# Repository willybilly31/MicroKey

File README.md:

# MicroKey
ATmega32U4-AU based micro controller with the sole purpose of emulating keyboard and mouse input. This project was made for Hack Club forge. The idea came to me when i was playing with my Esp32-S3 and thought the keyboard emulation with HID was cool, but the form factor of the Esp32 was too big and i also wanted to make my own devboard and thought this would be simple.

## Hardware
- ATmega32U4-AU
- Power Led
- User input Led
- USB C receptacle
- 16mhz Crystal
- Generic 2x3 header for bootloader

## Features
- HID emulation with the ATmega32U4-AU
- User input light

## Screenshots

## BOM 
﻿<table>
  <thead>
    <tr>
      <th>Designator</th>
      <th>Footprint</th>
      <th>Quantity</th>
      <th>Value</th>
      <th>LCSC Part #</th>
      <th>Minimum Price</th>
      <th>LCSC Link</th>
    </tr>
  </thead>
  <tbody>
    <tr>
      <td>C1, C2</td>
      <td>0603</td>
      <td>2</td>
      <td>27pF</td>
      <td>C1656</td>
      <td>0.60$</td>
      <td><a href="https://www.lcsc.com/product-detail/C1656.html">C1656</a></td>
    </tr>
    <tr>
      <td>C10, C3, C4, C5, C6, C9</td>
      <td>0603</td>
      <td>6</td>
      <td>100nF</td>
      <td>C1591</td>
      <td>0.28$</td>
      <td><a href="https://www.lcsc.com/product-detail/C1591.html">C1591</a></td>
    </tr>
    <tr>
      <td>C7</td>
      <td>0603</td>
      <td>1</td>
      <td>10uF</td>
      <td>C19702</td>
      <td>0.40$</td>
      <td><a href="https://www.lcsc.com/product-detail/C19702.html">C19702</a></td>
    </tr>
    <tr>
      <td>C8</td>
      <td>0603</td>
      <td>1</td>
      <td>1uF</td>
      <td>C15849</td>
      <td>0.87$</td>
      <td><a href="https://www.lcsc.com/product-detail/C15849.html">C15849</a></td>
    </tr>
    <tr>
      <td>D1</td>
      <td>0603</td>
      <td>1</td>
      <td>RED</td>
      <td>C2286</td>
      <td>0.0076$</td>
      <td><a href="https://www.lcsc.com/product-detail/C2286.html">C2286</a></td>
    </tr>
    <tr>
      <td>D2</td>
      <td>0603</td>
      <td>1</td>
      <td>BLUE</td>
      <td>C965807</td>
      <td>0.0043$</td>
      <td><a href="https://www.lcsc.com/product-detail/C965807.html">C965807</a></td>
    </tr>
    <tr>
      <td>J1</td>
      <td>GCT_USB4105-GF-A</td>
      <td>1</td>
      <td>USB_C_Receptacle_USB2.0_16P</td>
      <td>C5184243</td>
      <td></td>
      <td><a href="https://www.lcsc.com/product-detail/C5184243.html">C5184243</a></td>
    </tr>
    <tr>
      <td>J2</td>
      <td>AVR_ISP_2x3_Pogo_3p23x1p80</td>
      <td>1</td>
      <td>Conn_02x03_Odd_Even</td>
      <td></td>
      <td></td>
      <td></td>
    </tr>
    <tr>
      <td>R1, R2</td>
      <td>0603</td>
      <td>2</td>
      <td>5.1k</td>
      <td>C23186</td>
      <td>0.12$</td>
      <td><a href="https://www.lcsc.com/product-detail/C23186.html">C23186</a></td>
    </tr>
    <tr>
      <td>R3, R4</td>
      <td>0603</td>
      <td>2</td>
      <td>22</td>
      <td>C23345</td>
      <td>0.0018$</td>
      <td><a href="https://www.lcsc.com/product-detail/C23345.html">C23345</a></td>
    </tr>
    <tr>
      <td>R5, R6</td>
      <td>0603</td>
      <td>2</td>
      <td>1k</td>
      <td>C21190</td>
      <td>0.06$</td>
      <td><a href="https://www.lcsc.com/product-detail/C21190.html">C21190</a></td>
    </tr>
    <tr>
      <td>R7, R8</td>
      <td>0603</td>
      <td>2</td>
      <td>10k</td>
      <td>C25804</td>
      <td>0.09$</td>
      <td><a href="https://www.lcsc.com/product-detail/C25804.html">C25804</a></td>
    </tr>
    <tr>
      <td>U1</td>
      <td>TQFP-44_10x10mm_P0.8mm</td>
      <td>1</td>
      <td>ATmega32U4-A</td>
      <td>C44854</td>
      <td>6.94$</td>
      <td><a href="https://www.lcsc.com/product-detail/C44854.html">C44854</a></td>
    </tr>
    <tr>
      <td>Y1</td>
      <td>Crystal_SMD_3225-4Pin_3.2x2.5mm</td>
      <td>1</td>
      <td>16MHz</td>
      <td>C70562</td>
      <td>0.55$</td>
      <td><a href="https://www.lcsc.com/product-detail/C70562.html">C70562</a></td>
    </tr>
  </tbody>
</table>

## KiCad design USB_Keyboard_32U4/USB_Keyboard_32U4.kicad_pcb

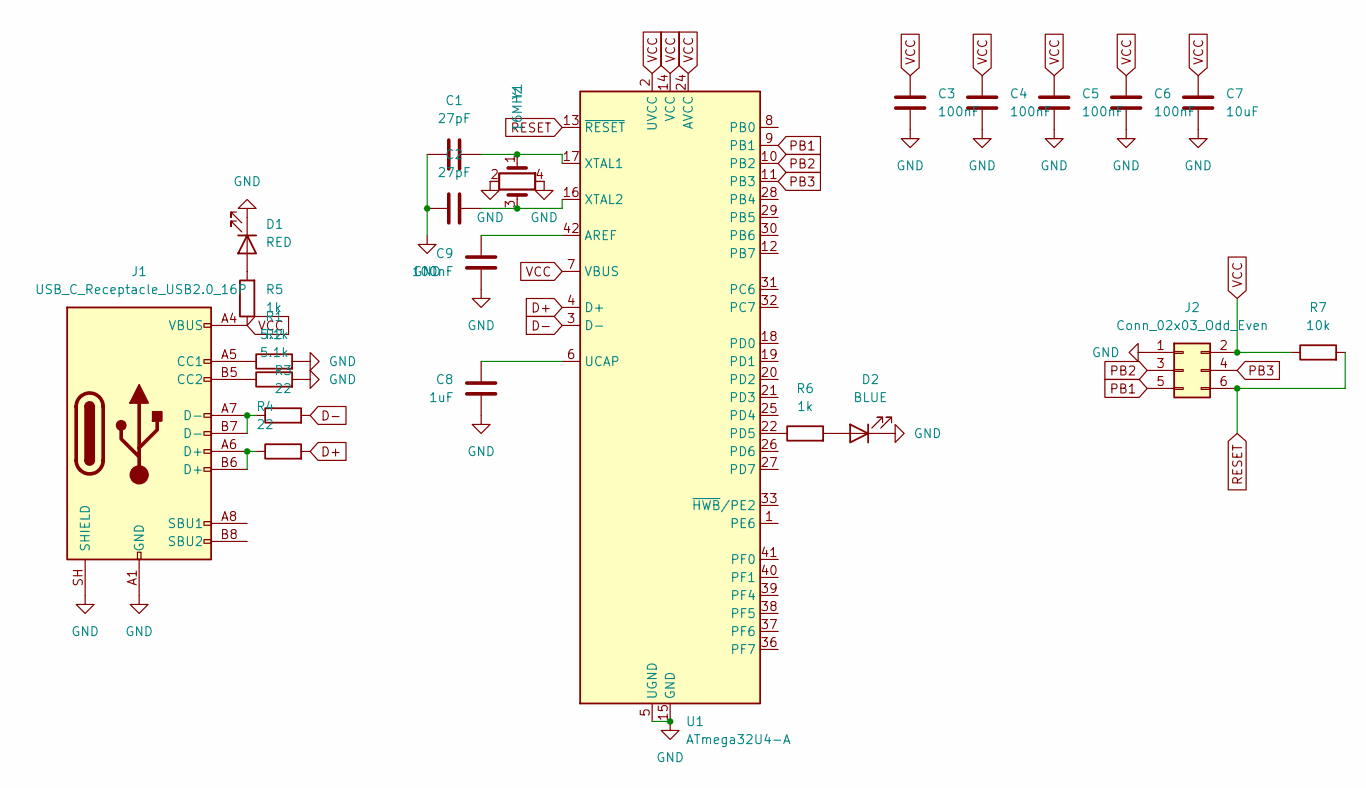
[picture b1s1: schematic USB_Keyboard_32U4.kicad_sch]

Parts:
C1, C2: 27pF; C_0603_1608Metric_Pad1.08x0.95mm_HandSolder
C3, C4, C5, C6, C9: 100nF; C_0603_1608Metric_Pad1.08x0.95mm_HandSolder
C7: 10uF; C_0603_1608Metric_Pad1.08x0.95mm_HandSolder
C8: 1uF; C_0603_1608Metric_Pad1.08x0.95mm_HandSolder
D1: RED; LED_0603_1608Metric_Pad1.05x0.95mm_HandSolder
D2: BLUE; LED_0603_1608Metric_Pad1.05x0.95mm_HandSolder
J1: USB_C_Receptacle_USB2.0_16P; GCT_USB4105-GF-A
J2: Conn_02x03_Odd_Even; AVR_ISP_2x3_Pogo_3p23x1p80
R1, R2: 5.1k; R_0603_1608Metric_Pad0.98x0.95mm_HandSolder
R3, R4: 22; R_0603_1608Metric_Pad0.98x0.95mm_HandSolder
R5, R6: 1k; R_0603_1608Metric_Pad0.98x0.95mm_HandSolder
R7: 10k; R_0603_1608Metric_Pad0.98x0.95mm_HandSolder
U1: ATmega32U4-A; TQFP-44_10x10mm_P0.8mm
Y1: 16MHz; Crystal_SMD_3225-4Pin_3.2x2.5mm

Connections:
D+: R4.2, U1.4 (D+)
D-: R3.2, U1.3 (D-)
GND: C1.1, C2.1, C3.2, C4.2, C5.2, C6.2, C7.2, C8.2, C9.2, D1.1 (K), D2.1 (K), J1.A1 (GND), J1.A12 (GND), J1.B1 (GND), J1.B12 (GND), J1.SH (SHIELD), J2.1, R1.2, R2.2, U1.5 (UGND), U1.15 (GND), U1.23 (GND), U1.35 (GND), U1.43 (GND), Y1.2, Y1.4; also elsewhere on the board
unnamed: D1.2 (A), R5.2
unnamed: D2.2 (A), R6.2
unnamed: J1.A5 (CC1), R1.1
unnamed: J1.B5 (CC2), R2.1
unnamed: J1.A6 (D+), J1.B6 (D+), R4.1
unnamed: J1.A7 (D-), J1.B7 (D-), R3.1
unnamed: C9.1, U1.42 (AREF)
unnamed: R6.1, U1.22 (PD5)
unnamed: C8.1, U1.6 (UCAP)
unnamed: C1.2, U1.17 (XTAL1), Y1.1
unnamed: C2.2, U1.16 (XTAL2), Y1.3
PB1: J2.5, U1.9 (PB1)
PB2: J2.3, U1.10 (PB2)
PB3: J2.4, U1.11 (PB3)
RESET: J2.6, R7.2, U1.13 (~RESET)
VCC: C3.1, C4.1, C5.1, C6.1, C7.1, J1.A4 (VBUS), J1.A9 (VBUS), J1.B4 (VBUS), J1.B9 (VBUS), J2.2, R5.1, R7.1, U1.2 (UVCC), U1.7 (VBUS), U1.14 (VCC), U1.24 (AVCC), U1.34 (VCC), U1.44 (AVCC); also elsewhere on the board

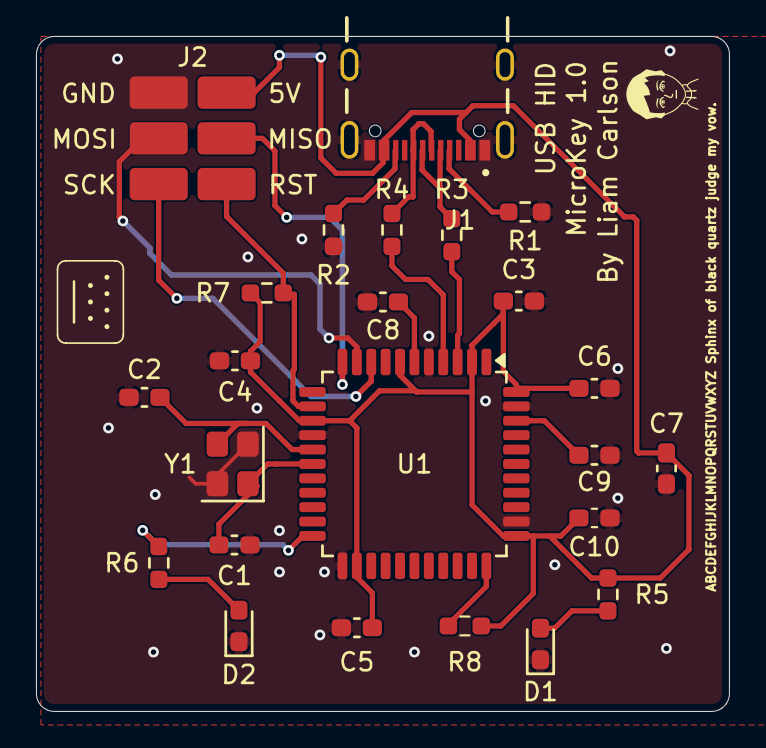
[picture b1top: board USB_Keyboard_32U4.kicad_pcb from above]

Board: 2 copper layers, 38.5 x 37.5 mm, 26 parts (0 on the bottom side), 19 nets.

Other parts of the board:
C10: 100nF; C_0603_1608Metric_Pad1.08x0.95mm_HandSolder
GKB1: Keyboard_Lucide_10mm_Silkscreen
R8: 10k; R_0603_1608Metric_Pad0.98x0.95mm_HandSolder
mii: LOGO; MicroKey_Logo

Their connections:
GND: C10.2; also elsewhere on the board
VCC: C10.1, R8.1; also elsewhere on the board

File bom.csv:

Designator,Footprint,Quantity,Value,LCSC Part #,Minimum Price,LCSC Link
"C1, C2",0603,2,27pF,C1656,0.60$,https://www.lcsc.com/product-detail/C1656.html
"C10, C3, C4, C5, C6, C9",0603,6,100nF,C1591,0.28$,https://www.lcsc.com/product-detail/C1591.html
C7,0603,1,10uF,C19702,0.40$,https://www.lcsc.com/product-detail/C19702.html
C8,0603,1,1uF,C15849,0.87$,https://www.lcsc.com/product-detail/C15849.html
D1,0603,1,RED,C2286,0.0076$,https://www.lcsc.com/product-detail/C2286.html
D2,0603,1,BLUE,C965807,0.0043$,https://www.lcsc.com/product-detail/C965807.html
J1,GCT_USB4105-GF-A,1,USB_C_Receptacle_USB2.0_16P,C3020560,1.31$,https://www.lcsc.com/product-detail/C3020560.html
J2,AVR_ISP_2x3_Pogo_3p23x1p80,1,Conn_02x03_Odd_Even,,,
"R1, R2",0603,2,5.1k,C23186,0.12$,https://www.lcsc.com/product-detail/C23186.html
"R3, R4",0603,2,22,C23345,0.0018$,https://www.lcsc.com/product-detail/C23345.html
"R5, R6",0603,2,1k,C21190,0.06$,https://www.lcsc.com/product-detail/C21190.html
"R7, R8",0603,2,10k,C25804,0.09$,https://www.lcsc.com/product-detail/C25804.html
U1,TQFP-44_10x10mm_P0.8mm,1,ATmega32U4-A,C44854,6.94$,https://www.lcsc.com/product-detail/C44854.html
Y1,Crystal_SMD_3225-4Pin_3.2x2.5mm,1,16MHz,C70562,0.55$,https://www.lcsc.com/product-detail/C70562.html

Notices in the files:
parts and their libraries:
Keyboard graphic adapted from Lucide keyboard.svg, nominal 10 x 8 mm; front silkscreen only, no pads. ISC License; copyright 2026 Lucide Icons and Contributors. Source: https://github.com/lucide-icons/lucide/blob/main/icons/keyboard.svg
